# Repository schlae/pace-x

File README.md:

# Pace-X INS8900 Computer

(Still under development)

The INS8900 is a NMOS version of National Semiconductor's PACE microprocessor.
This was (probably) the first 16-bit microprocessor to hit the market in the
mid 1970s.

This is a very simple computer built around this chip. Features include

* 2MHz operation
* 128K words of RAM
* Up to 128K words of ROM
* 8250 (or compatible) UART
* Software controlled status LEDs
* 12VDC input

Note that the memory split between RROM and RAM is controlled by a PAL that
sets up the memory map. Banking is supported using up to three flag outputs
(F11, F12, F13) on the CPU. The current memory map is:

* 0000 to 001FF - ROM (can be swapped out with RAM using F11)
* 0200 to FDFF - RAM
* FE00 to FFFF - UART (mirrored a bunch of times)

UART access is easiest at FF00 (absolute). But it can also be done from the
zero page when BPS is brought high. This can be activated using F12.

The PAL code is assembled using `galette`. [site](https://github.com/simon-frankau/galette)

The assembly code for the INS8900 is assembled using `asl` [site]([http://john.ccac.rwth-aachen.de:8000/as/)

## Assembling the code

CPU source code is assembled as follows

```
asl test.asm -L
p2bin test.p test.bin
python3 split.py
```

The result are two files, `high.bin` and `low.bin` which need to be programmed
into two EPROMS or EEPROMS. You can do this with a TL866 using `minipro`. For example, using two MX28F1000P EEPROM chips:

```
minipro -p MX28F1000P -w low.bin -s
```
(swap the chips)
```
minipro -p MX28F1000P -w high.bin -s
```

To assemble and program the GAL, run
```
galette addr_decoder.pld
minipro -p ATF16V8B -w addr_decoder.jed
```

That's all for now!

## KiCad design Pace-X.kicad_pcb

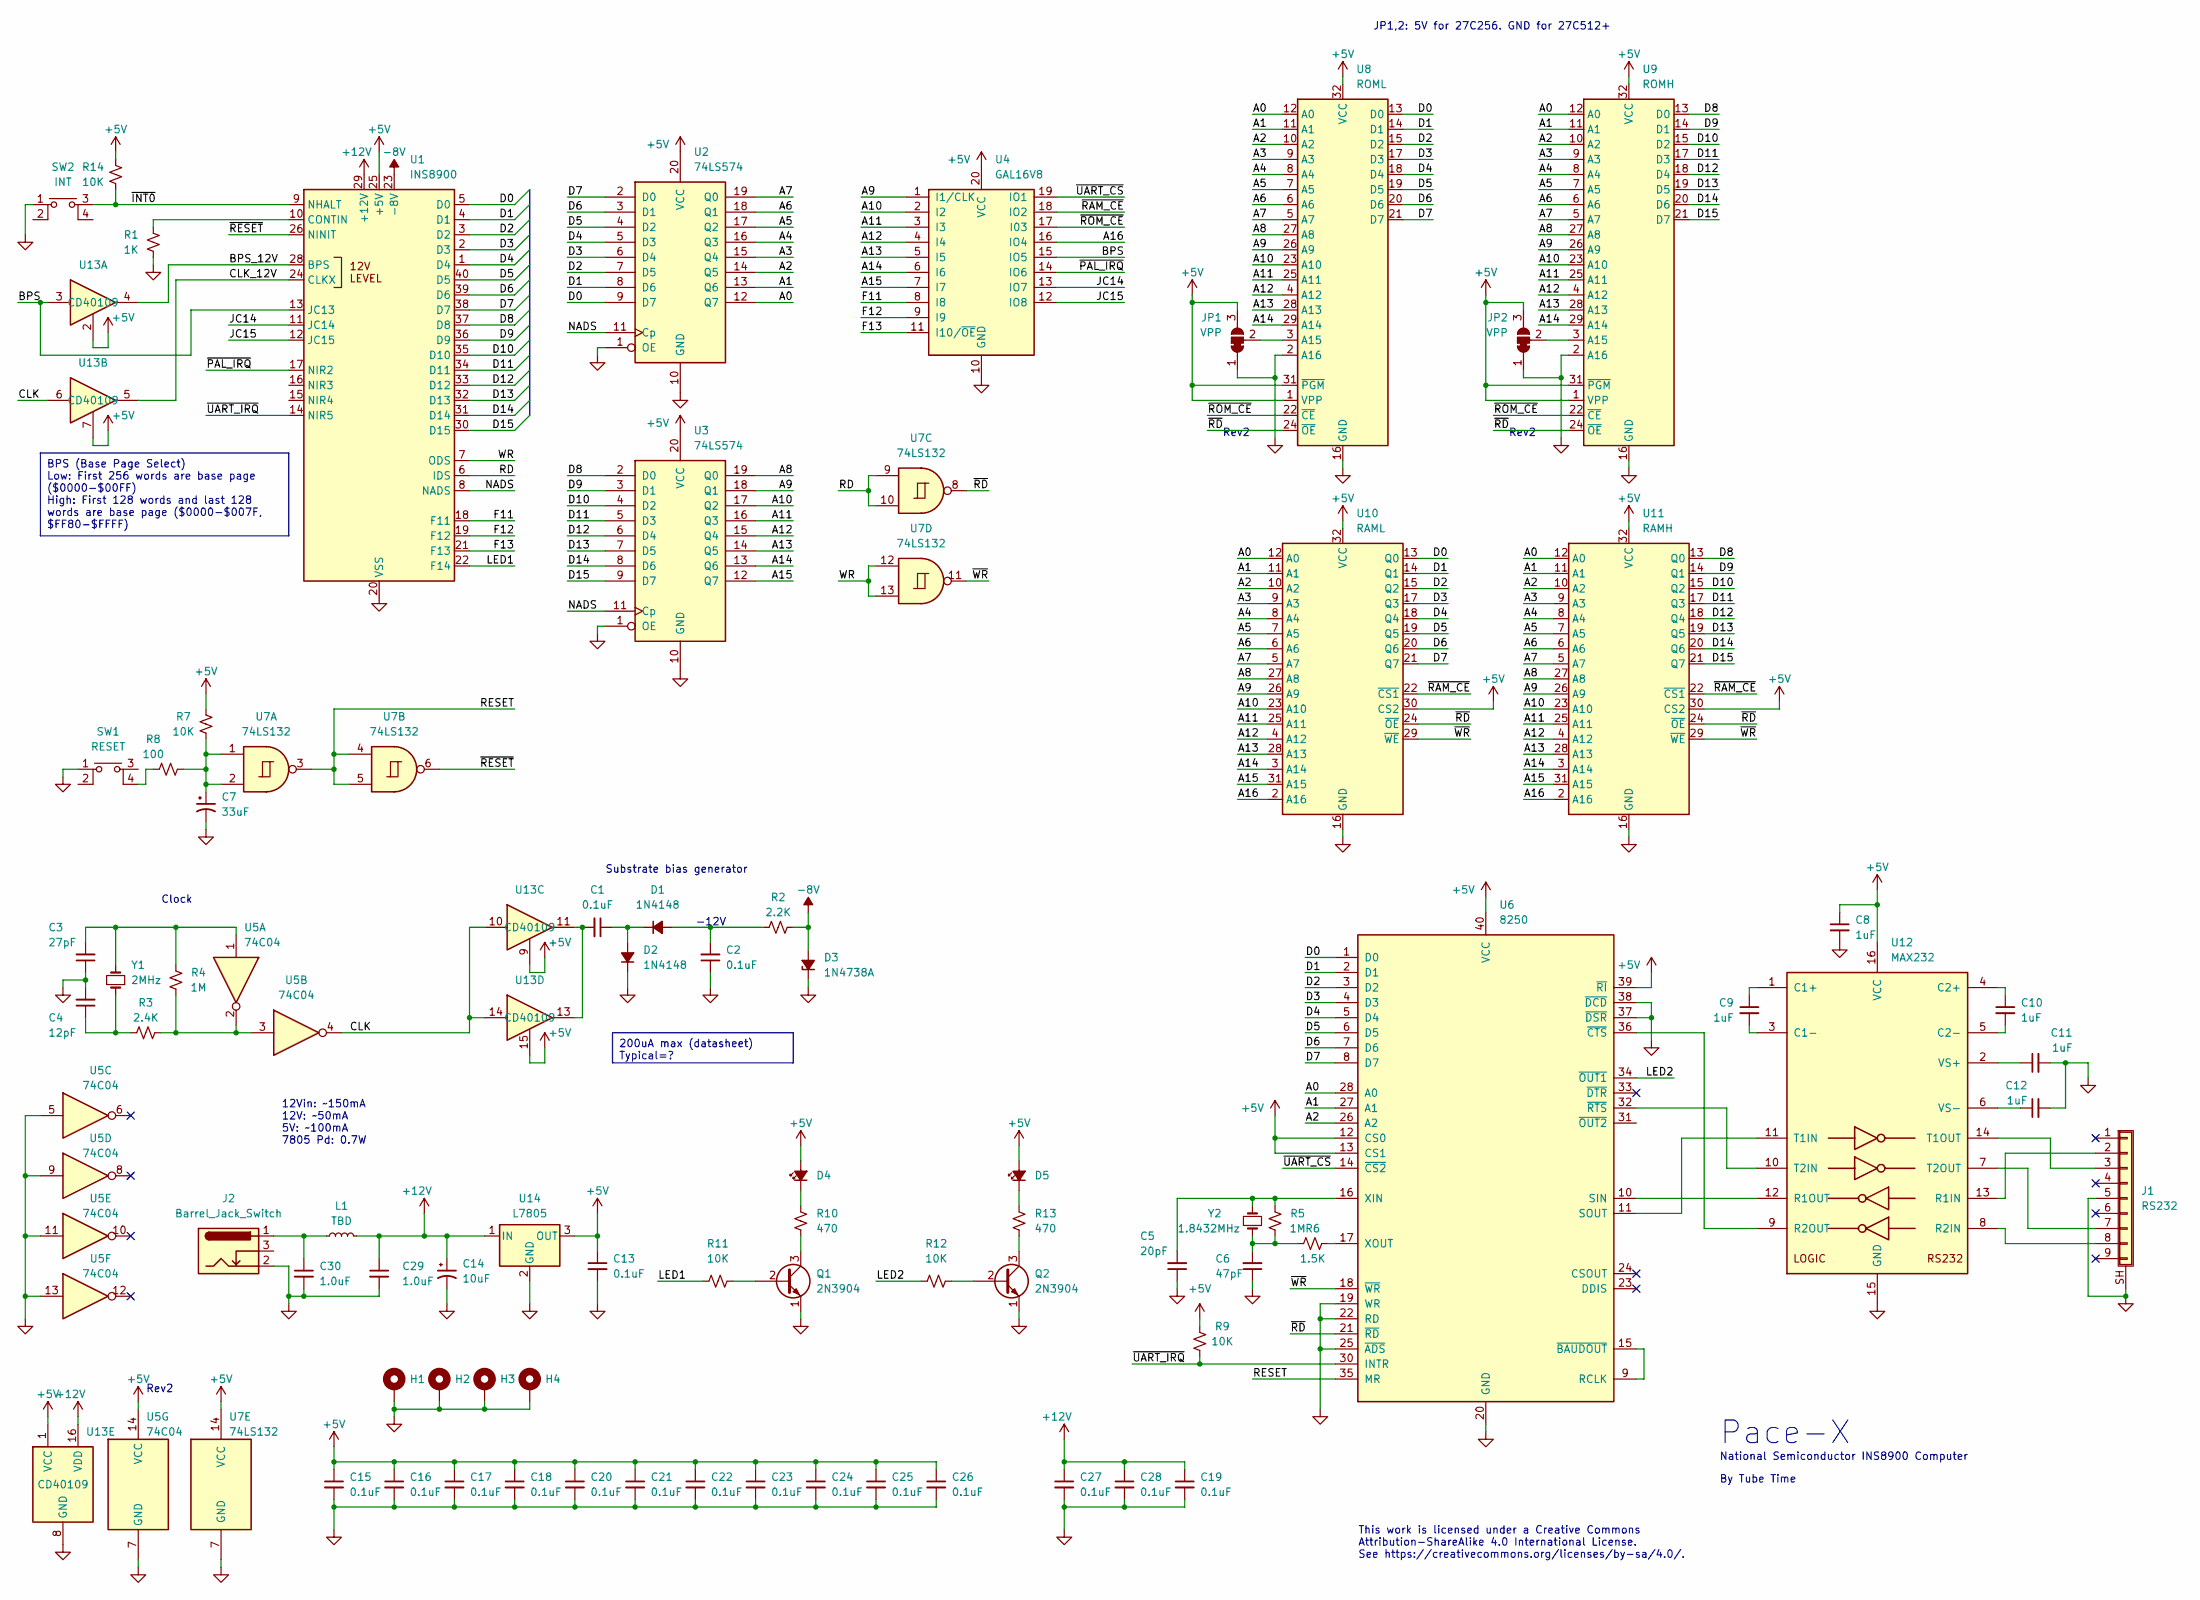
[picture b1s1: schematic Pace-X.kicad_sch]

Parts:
C1, C2, C13, C15, C16, C17, C18, C19, C20, C21, C22, C23, C24, C25, C26, C27, C28: 0.1uF; CAPAC200
C3: 27pF; CAPAC200
C4: 12pF; CAPAC200
C5: 20pF; CAPAC200
C6: 47pF; CAPAC200
C7: 33uF; CAPAE200P500X1100
C8, C9, C10, C11, C12: 1uF; CAPAC200
C14: 10uF; CAPAE200P500X1100
C29, C30: 1.0uF; CAPAC200
D1, D2: 1N4148; DIOA500
D3: 1N4738A; DIOA500
D4, D5: LED; LED_D5.0mm
H1, H2, H3, H4: MountingHole_Pad; MountingHole_3.2mm_M3_ISO7380_Pad
J1: RS232; DB9FC2
J2: Barrel_Jack_Switch; CUI_PJ-002B
JP1, JP2: VPP; SolderJumper-3_P1.3mm_Bridged12_RoundedPad1.0x1.5mm_NumberL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
L1: TBD; L_Axial_L7.0mm_D3.3mm_P12.70mm_Horizontal_Fastron_MICC
Q1, Q2: 2N3904; TO-92_Inline
R1: 1K; RESA500
R2: 2.2K; RESA500
R3: 2.4K; RESA500
R4, R5: 1M; RESA500
R6: 1.5K; RESA500
R7, R9, R11, R12, R14: 10K; RESA500
R8: 100; RESA500
R10, R13: 470; RESA500
SW1: RESET; ESWITCH_TL1105
SW2: INT; ESWITCH_TL1105
U1: INS8900; DIP254P1524X635-40
U2, U3: 74LS574; DIP254P762X635-20
U4: GAL16V8; DIP254P762X635-20
U5: 74C04; DIP254P762X635-14
U6: 8250; DIP254P1524X635-40
U7: 74LS132; DIP254P762X635-14
U8: ROML; DIP254P1524X635-32
U9: ROMH; DIP254P1524X635-32
U10: RAML; DIP254P1524X635-32
U11: RAMH; DIP254P1524X635-32
U12: MAX232; DIP254P762X635-16
U13: CD40109; DIP254P762X635-16
U14: L7805; TO-220-3_Horizontal_TabDown
Y1: 2MHz; Crystal_HC49-U_Vertical
Y2: 1.8432MHz; Crystal_HC49-U_Vertical

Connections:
-8V: D3.2 (A), R2.2, U1.23 (-8V)
/A0: U2.12 (Q7), U6.28 (A0), U8.12 (A0), U9.12 (A0), U10.12 (A0), U11.12 (A0)
/A1: U2.13 (Q6), U6.27 (A1), U8.11 (A1), U9.11 (A1), U10.11 (A1), U11.11 (A1)
/A2: U2.14 (Q5), U6.26 (A2), U8.10 (A2), U9.10 (A2), U10.10 (A2), U11.10 (A2)
/A3: U2.15 (Q4), U8.9 (A3), U9.9 (A3), U10.9 (A3), U11.9 (A3)
/A4: U2.16 (Q3), U8.8 (A4), U9.8 (A4), U10.8 (A4), U11.8 (A4)
/A5: U2.17 (Q2), U8.7 (A5), U9.7 (A5), U10.7 (A5), U11.7 (A5)
/A6: U2.18 (Q1), U8.6 (A6), U9.6 (A6), U10.6 (A6), U11.6 (A6)
/A7: U2.19 (Q0), U8.5 (A7), U9.5 (A7), U10.5 (A7), U11.5 (A7)
/A8: U3.19 (Q0), U8.27 (A8), U9.27 (A8), U10.27 (A8), U11.27 (A8)
/A9: U3.18 (Q1), U4.1 (I1/CLK), U8.26 (A9), U9.26 (A9), U10.26 (A9), U11.26 (A9)
/A10: U3.17 (Q2), U4.2 (I2), U8.23 (A10), U9.23 (A10), U10.23 (A10), U11.23 (A10)
/A11: U3.16 (Q3), U4.3 (I3), U8.25 (A11), U9.25 (A11), U10.25 (A11), U11.25 (A11)
/A12: U3.15 (Q4), U4.4 (I4), U8.4 (A12), U9.4 (A12), U10.4 (A12), U11.4 (A12)
/A13: U3.14 (Q5), U4.5 (I5), U8.28 (A13), U9.28 (A13), U10.28 (A13), U11.28 (A13)
/A14: U3.13 (Q6), U4.6 (I6), U8.29 (A14), U9.29 (A14), U10.3 (A14), U11.3 (A14)
/A15: U3.12 (Q7), U4.7 (I7), U10.31 (A15), U11.31 (A15)
/A16: U4.16 (IO4), U10.2 (A16), U11.2 (A16)
/BPS: U1.13 (JC13), U4.15 (IO5), U13.3
/BPS_12V: U1.28 (BPS), U13.4
/CLK: U5.4, U13.6, U13.10, U13.14
/CLK_12V: U1.24 (CLKX), U13.5
/D0: U1.5 (D0), U2.9 (D7), U6.1 (D0), U8.13 (D0), U10.13 (Q0)
/D1: U1.4 (D1), U2.8 (D6), U6.2 (D1), U8.14 (D1), U10.14 (Q1)
/D2: U1.3 (D2), U2.7 (D5), U6.3 (D2), U8.15 (D2), U10.15 (Q2)
/D3: U1.2 (D3), U2.6 (D4), U6.4 (D3), U8.17 (D3), U10.17 (Q3)
/D4: U1.1 (D4), U2.5 (D3), U6.5 (D4), U8.18 (D4), U10.18 (Q4)
/D5: U1.40 (D5), U2.4 (D2), U6.6 (D5), U8.19 (D5), U10.19 (Q5)
/D6: U1.39 (D6), U2.3 (D1), U6.7 (D6), U8.20 (D6), U10.20 (Q6)
/D7: U1.38 (D7), U2.2 (D0), U6.8 (D7), U8.21 (D7), U10.21 (Q7)
/D8: U1.37 (D8), U3.2 (D0), U9.13 (D0), U11.13 (Q0)
/D9: U1.36 (D9), U3.3 (D1), U9.14 (D1), U11.14 (Q1)
/D10: U1.35 (D10), U3.4 (D2), U9.15 (D2), U11.15 (Q2)
/D11: U1.34 (D11), U3.5 (D3), U9.17 (D3), U11.17 (Q3)
/D12: U1.33 (D12), U3.6 (D4), U9.18 (D4), U11.18 (Q4)
/D13: U1.32 (D13), U3.7 (D5), U9.19 (D5), U11.19 (Q5)
/D14: U1.31 (D14), U3.8 (D6), U9.20 (D6), U11.20 (Q6)
/D15: U1.30 (D15), U3.9 (D7), U9.21 (D7), U11.21 (Q7)
/F11: U1.18 (F11), U4.8 (I8)
/F12: U1.19 (F12), U4.9 (I9)
/F13: U1.21 (F13), U4.11 (I10/~OE)
/JC14: U1.11 (JC14), U4.13 (IO7)
/JC15: U1.12 (JC15), U4.12 (IO8)
/LED1: R11.2, U1.22 (F14)
/LED2: R12.2, U6.34 (~OUT1)
/NADS: U1.8 (NADS), U2.11 (Cp), U3.11 (Cp)
/RD: U1.6 (IDS), U7.9, U7.10
/RESET: U6.35 (MR), U7.3, U7.4, U7.5
/WR: U1.7 (ODS), U7.12, U7.13
/~INT0: R14.1, SW2.3, U1.9 (NHALT)
/~PAL_IRQ: U1.17 (NIR2), U4.14 (IO6)
/~RAM_CE: U4.18 (IO2), U10.22 (~CS1), U11.22 (~CS1)
/~RESET: U1.26 (NINIT), U7.6
/~ROM_CE: U4.17 (I03), U8.22 (~CE), U9.22 (~CE)
/~UART_CS: U4.19 (IO1), U6.14 (~CS2)
/~UART_IRQ: R9.1, U1.14 (NIR5), U6.30 (INTR)
/~WR: U6.18 (~WR), U7.11, U10.29 (~WE), U11.29 (~WE)
unnamed: C1.2, U13.11, U13.13
unnamed: C3.2, R4.1, U5.1, Y1.2
unnamed: C4.1, R3.1, Y1.1
unnamed: C7.1, R7.1, R8.1, U7.1, U7.2
unnamed: C30.1, J2.1, L1.1
unnamed: C2.2, D1.2 (A), R2.1
unnamed: C1.1, D1.1 (K), D2.2 (A)
unnamed: D4.1 (K), R10.1
unnamed: D5.1 (K), R13.1
unnamed: J1.2, U12.13 (R1IN)
unnamed: J1.3, U12.14 (T1OUT)
unnamed: J1.7, U12.7 (T2OUT)
unnamed: J1.8, U12.8 (R2IN)
unnamed: JP1.2 (C), U8.3 (A15)
unnamed: JP2.2 (C), U9.3 (A15)
unnamed: Q1.2 (B), R11.1
unnamed: Q1.3 (C), R10.2
unnamed: Q2.2 (B), R12.1
unnamed: Q2.3 (C), R13.2
unnamed: R3.2, R4.2, U5.2, U5.3
unnamed: R8.2, SW1.4
unnamed: R1.1, U1.10 (CONTIN)
unnamed: U6.9 (RCLK), U6.15 (~BAUDOUT)
unnamed: C5.2, R5.1, U6.16 (XIN), Y2.2
unnamed: C9.1, U12.1 (C1+)
unnamed: C9.2, U12.3 (C1-)
unnamed: C10.1, U12.4 (C2+)
unnamed: C10.2, U12.5 (C2-)
unnamed: U6.10 (SIN), U12.12 (R1OUT)
unnamed: U6.36 (~CTS), U12.9 (R2OUT)
unnamed: U6.11 (SOUT), U12.11 (T1IN)
unnamed: U6.32 (~RTS), U12.10 (T2IN)
unnamed: C11.1, U12.2 (VS+)
unnamed: C12.1, U12.6 (VS-)

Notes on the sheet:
BPS (Base Page Select) Low: First 256 words are base page ($0000-$00FF) High: First 128 words and last 128 words are base page ($0000-$007F, $FF80-$FFFF)
200uA max (datasheet) Typical=?
JP1,2: 5V for 27C256. GND for 27C512+
National Semiconductor INS8900 Computer
Rev2
12Vin: ~150mA 12V: ~50mA 5V: ~100mA 7805 Pd: 0.7W
Clock
Pace-X
-12V
Substrate bias generator
This work is licensed under a Creative Commons Attribution-ShareAlike 4.0 International License. See https://creativecommons.org/licenses/by-sa/4.0/.
By Tube Time

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
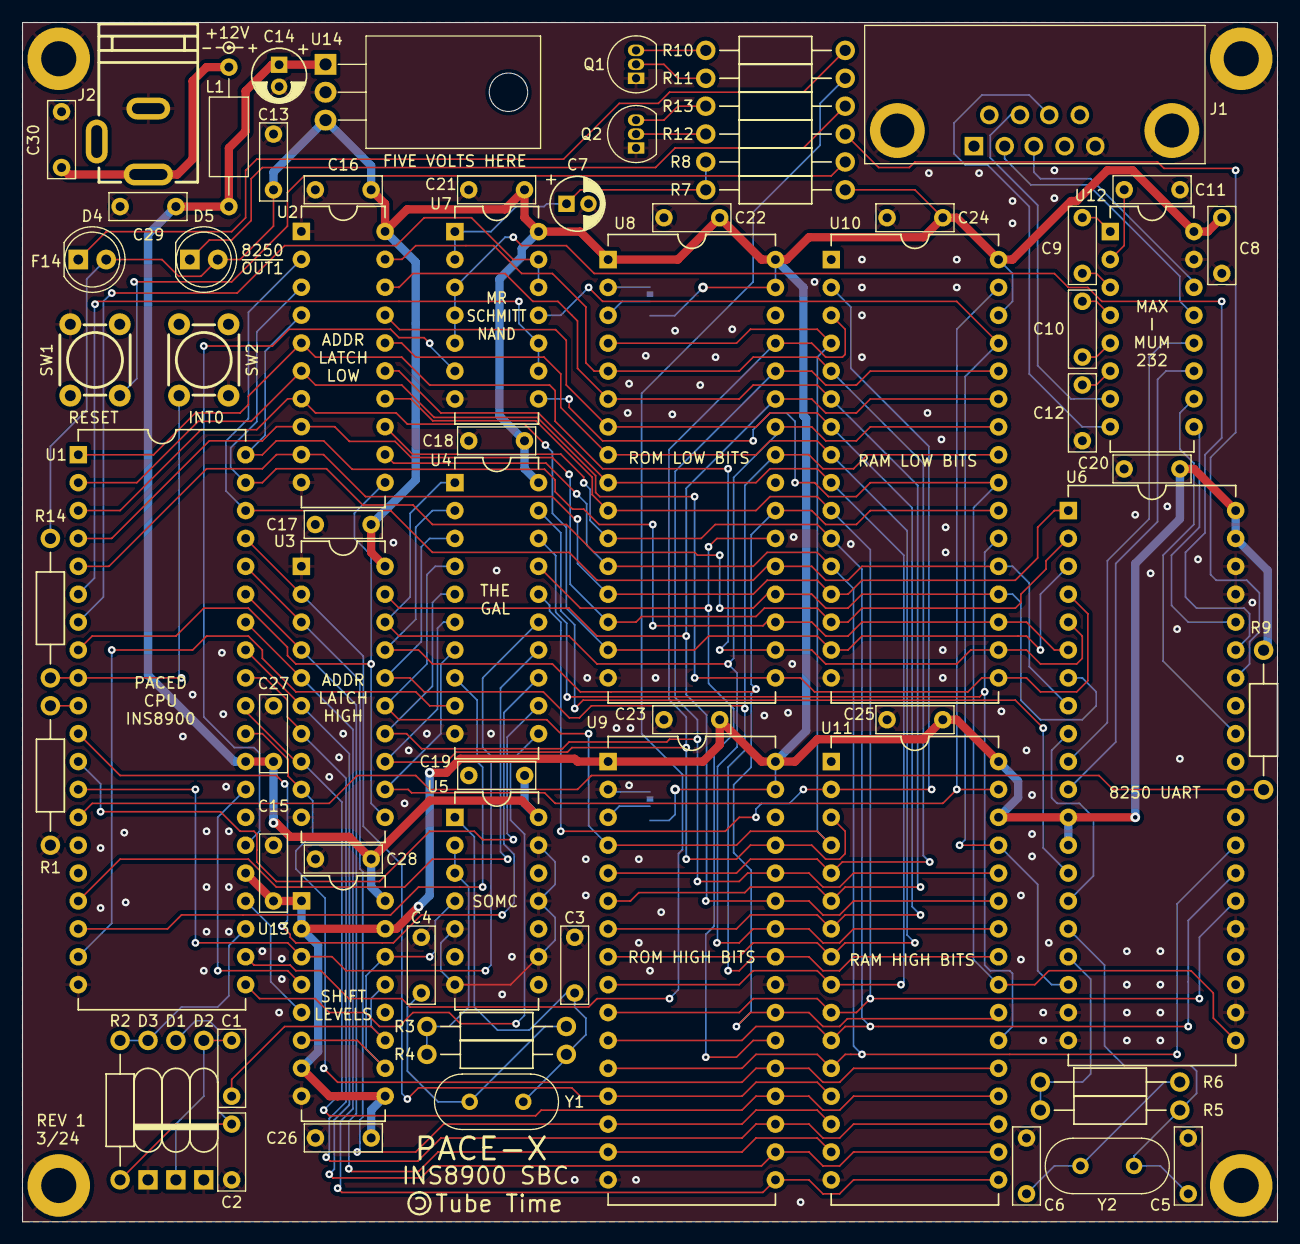
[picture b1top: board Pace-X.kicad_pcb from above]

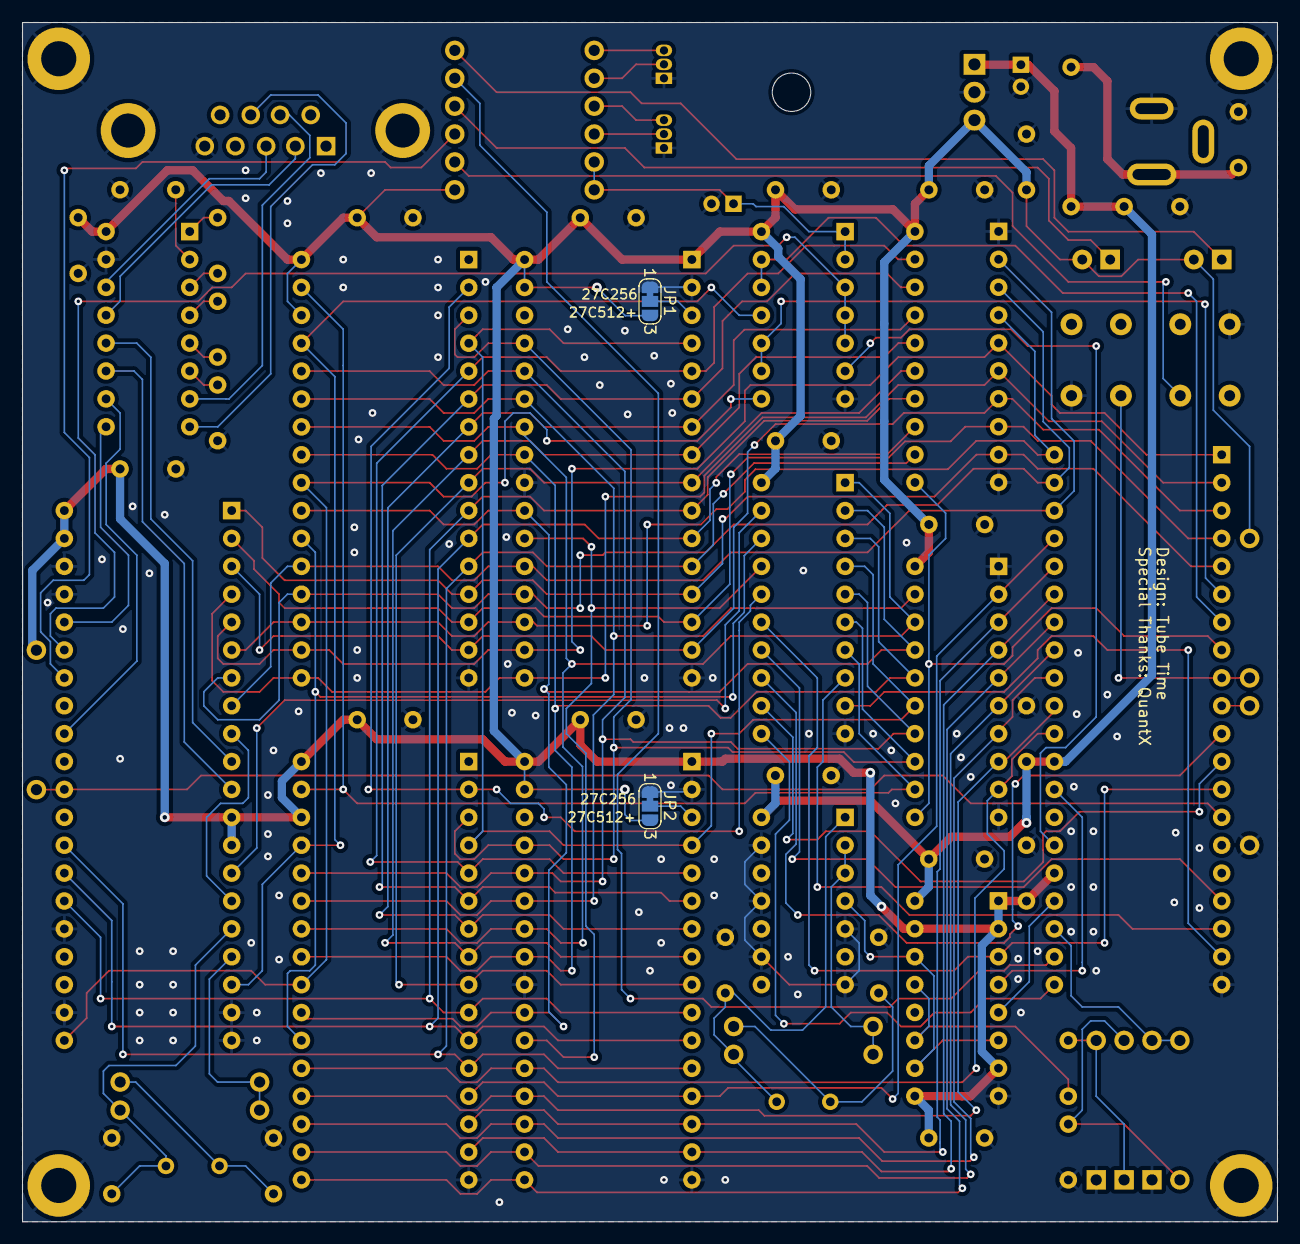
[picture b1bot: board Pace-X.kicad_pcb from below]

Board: 2 copper layers, 114.3 x 109.2 mm, 78 parts (2 on the bottom side), 97 nets.

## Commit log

2024-04-02 initial pld and firmware
